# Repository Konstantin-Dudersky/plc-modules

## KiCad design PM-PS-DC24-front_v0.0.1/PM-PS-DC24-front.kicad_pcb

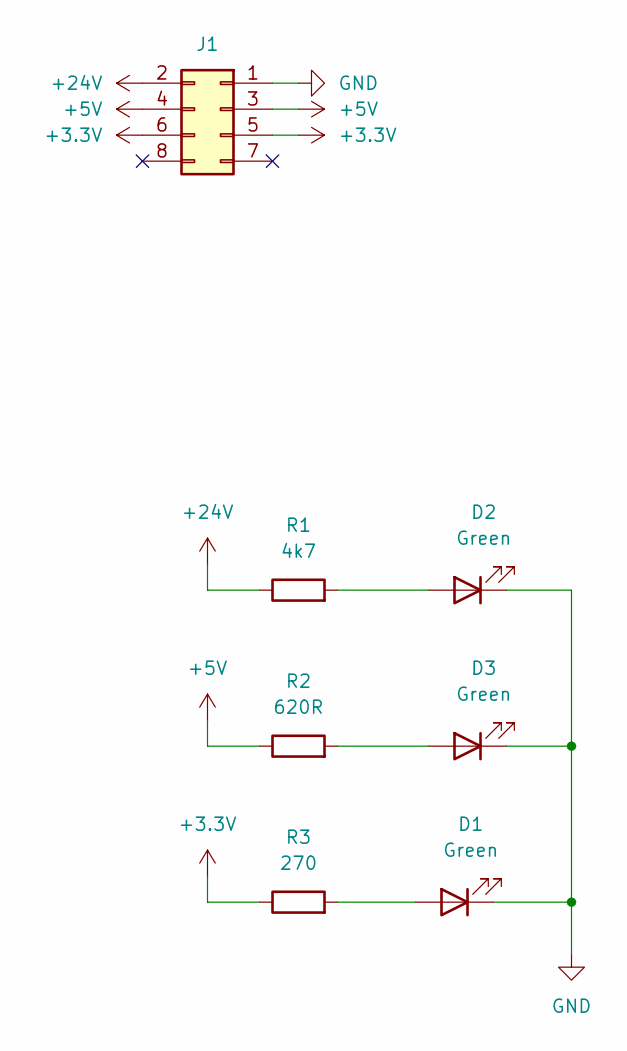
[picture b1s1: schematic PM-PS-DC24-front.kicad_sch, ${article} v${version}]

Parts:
D1, D2, D3: Green; LED_1206_3216Metric_ReverseMount_Hole1.8x2.4mm; part_ipn LED_green_1206_reverse
J1: PinHeader_02x04_P2.54_THT_angle; PinHeader_2x04_P2.54mm_Horizontal; part_ipn PinHeader_02x04_P2.54_THT_angle
R1: 4k7; R_1206_3216Metric_Pad1.30x1.75mm_HandSolder; part_ipn R_4k7_1206_1%
R2: 620R; R_1206_3216Metric_Pad1.30x1.75mm_HandSolder; part_ipn R_620R_1206_1%
R3: 270; R_1206_3216Metric_Pad1.30x1.75mm_HandSolder; part_ipn R_270_1206_1%

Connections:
+3.3V: J1.5, J1.6, R3.1
+5V: J1.3, J1.4, R2.1
+24V: J1.2, R1.1
GND: D1.1 (K), D2.1 (K), D3.1 (K), J1.1
unnamed: D1.2 (A), R3.2
unnamed: D2.2 (A), R1.2
unnamed: D3.2 (A), R2.2

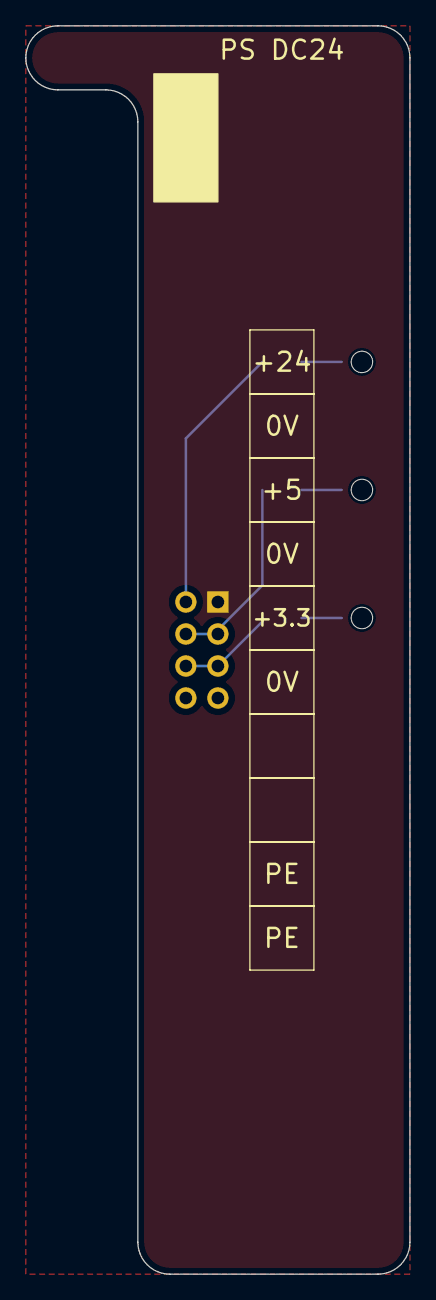
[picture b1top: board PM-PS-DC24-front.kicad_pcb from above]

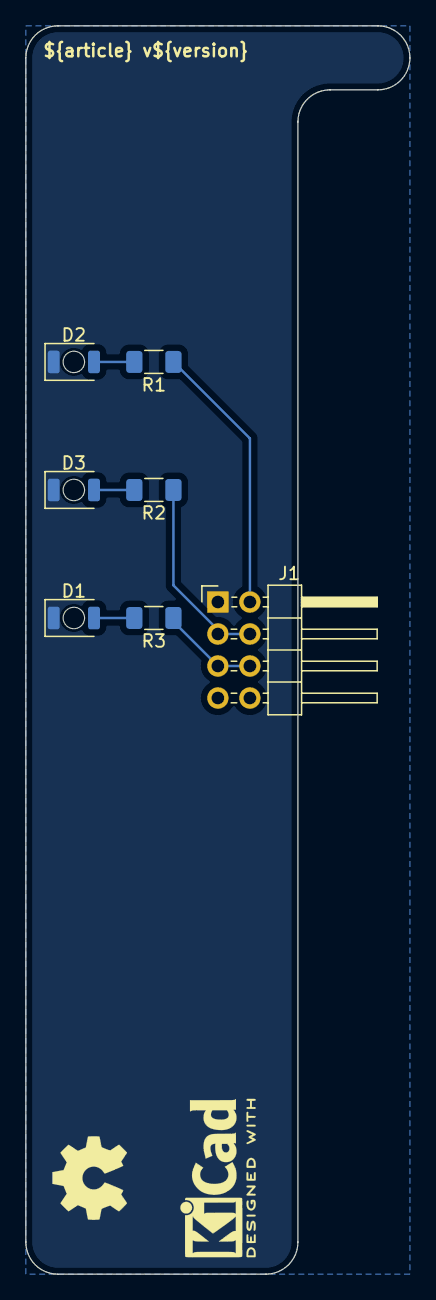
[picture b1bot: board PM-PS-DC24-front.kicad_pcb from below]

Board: 2 copper layers, 30.5 x 99.1 mm, 8 parts (8 on the bottom side), 7 nets.

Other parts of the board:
Logo_kicad: KiCad-Logo2_5mm_SilkScreen

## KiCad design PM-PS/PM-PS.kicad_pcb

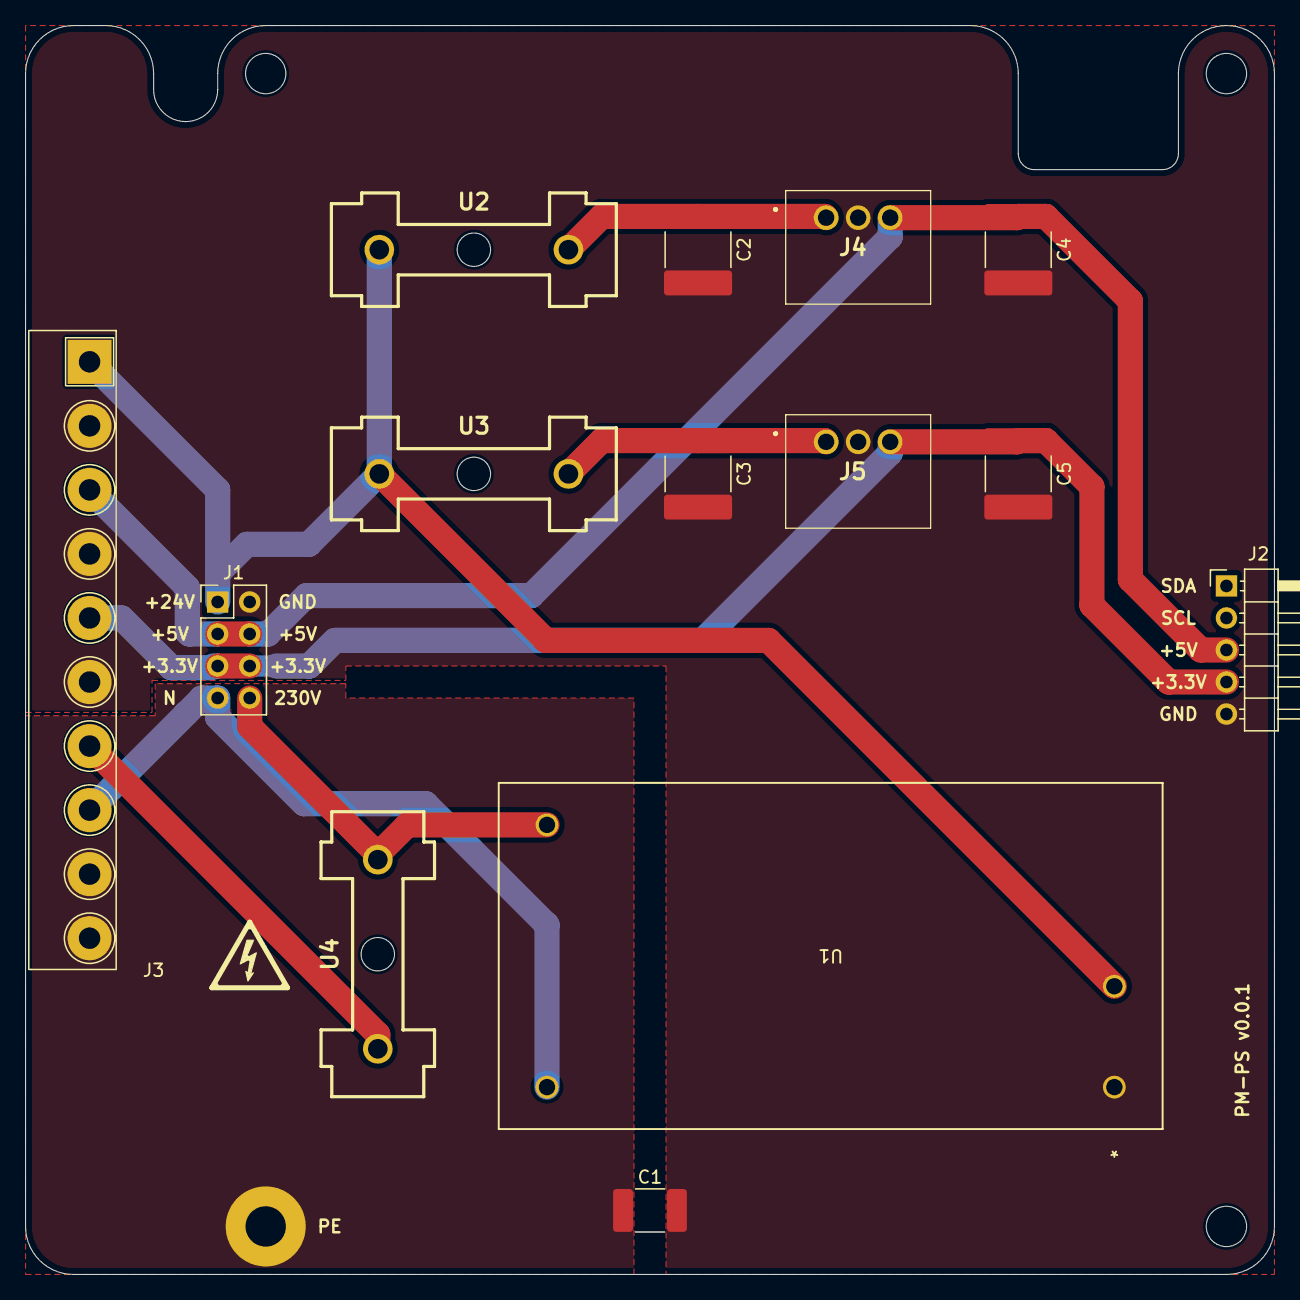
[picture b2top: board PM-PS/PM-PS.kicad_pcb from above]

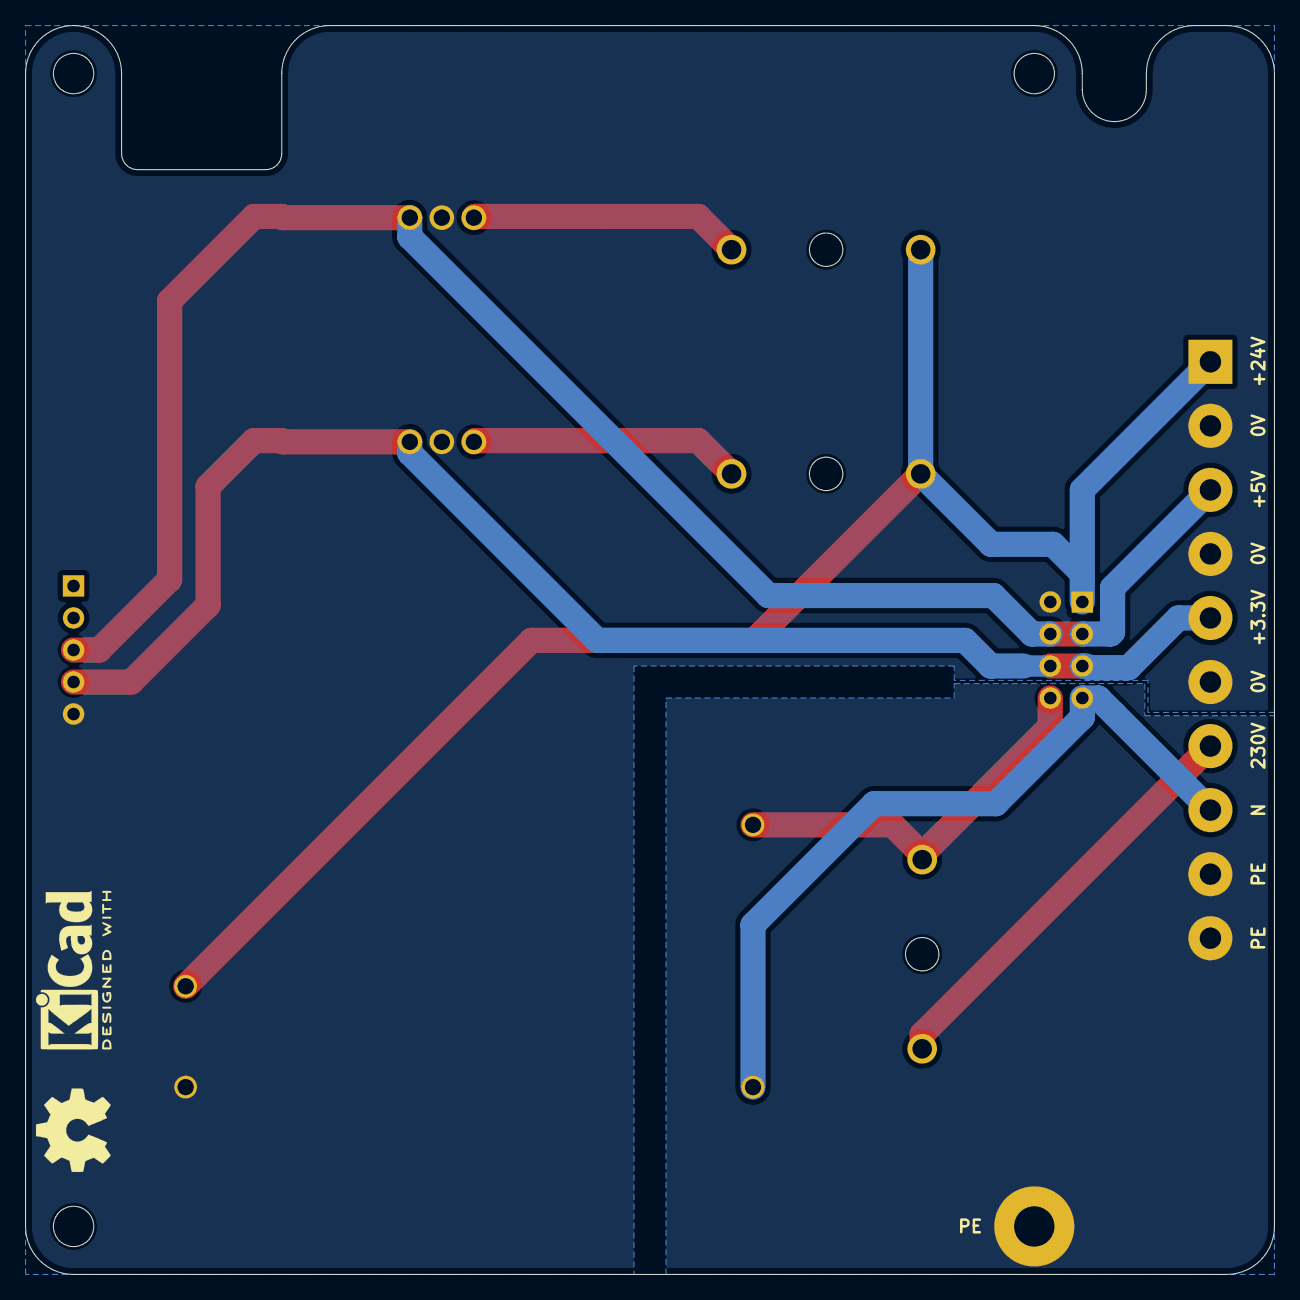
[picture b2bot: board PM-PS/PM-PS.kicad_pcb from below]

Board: 2 copper layers, 99.1 x 99.1 mm, 20 parts (2 on the bottom side), 10 nets.

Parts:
C1: 4.7nF 2kV; C_1812_4532Metric_Pad1.57x3.40mm_HandSolder
C2, C3, C4, C5: 22uF; C_2220_5750Metric_Pad1.97x5.40mm_HandSolder
H1, H2, H3: MountingHole; MountingHole_3.2mm_M3
J1: PM-front-02x04
J2: PinHeader_01x05_P2.54_THT_angle; PinHeader_1x05_P2.54mm_Horizontal
J3: 2EDGR-5.08-10P; Degson_2EDGR-5.08-10P
J4: K7805-2000R3
J5: K7803-2000R3; K7805-2000R3
PE1: PE
U1: IRM-20-24; IRM-20-24_MWU
U2, U3, U4: 64900001039; Fuseholder
kicad_logo: KiCad-Logo2_5mm_SilkScreen
oshw_logo: OSHW-Symbol_6.7x6mm_SilkScreen

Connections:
230V: J1.8, U1.3 (AC/L), U4.2
+3.3V: C5.1, J1.5, J1.6, J2.4, J3.5, J5.3 (+VO)
+5V: C4.1, J1.3, J1.4, J2.3, J3.3, J4.3 (+VO)
+24V: J1.1, J3.1, U1.2 (V+), U2.1, U3.1
GND: C1.2, C2.2, C3.2, C4.2, C5.2, J1.2, J2.5, J3.2, J3.4, J3.6, J4.2 (GND), J5.2 (GND), U1.1 (V-)
N: J1.7, J3.8, U1.4 (AC/N)
unnamed: J3.7, U4.1
unnamed: C2.1, J4.1 (VIN), U2.2
unnamed: C3.1, J5.1 (VIN), U3.2
PE: C1.1, J3.9, J3.10, PE1.1

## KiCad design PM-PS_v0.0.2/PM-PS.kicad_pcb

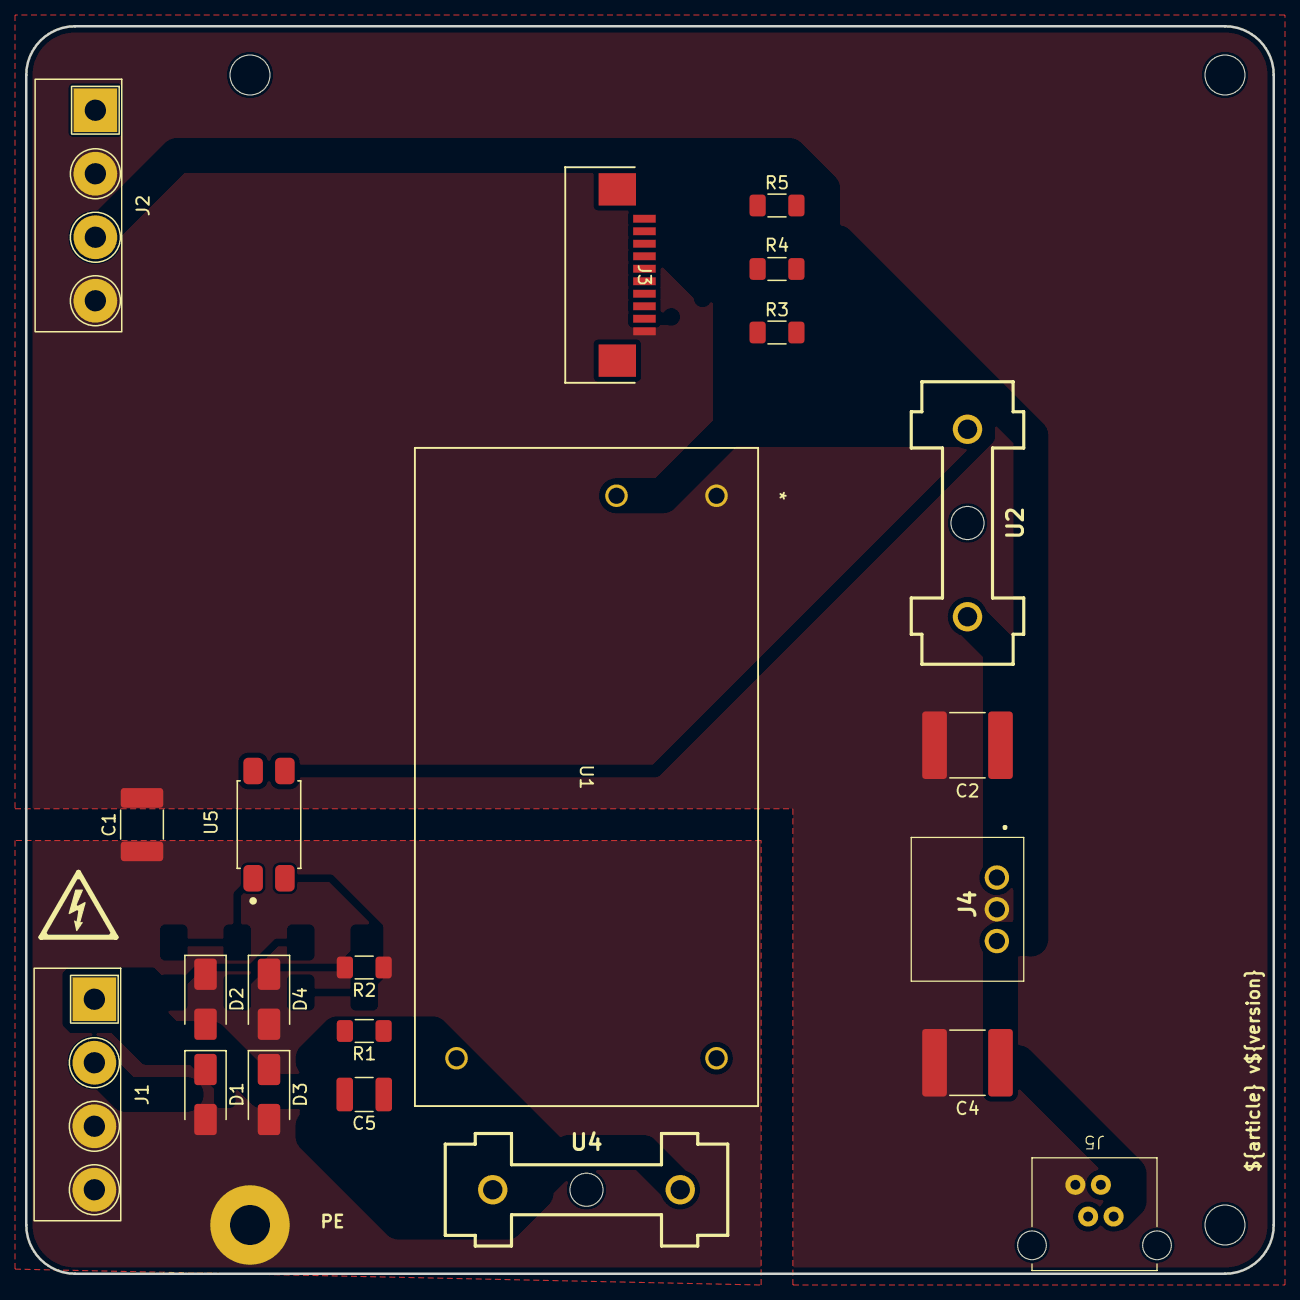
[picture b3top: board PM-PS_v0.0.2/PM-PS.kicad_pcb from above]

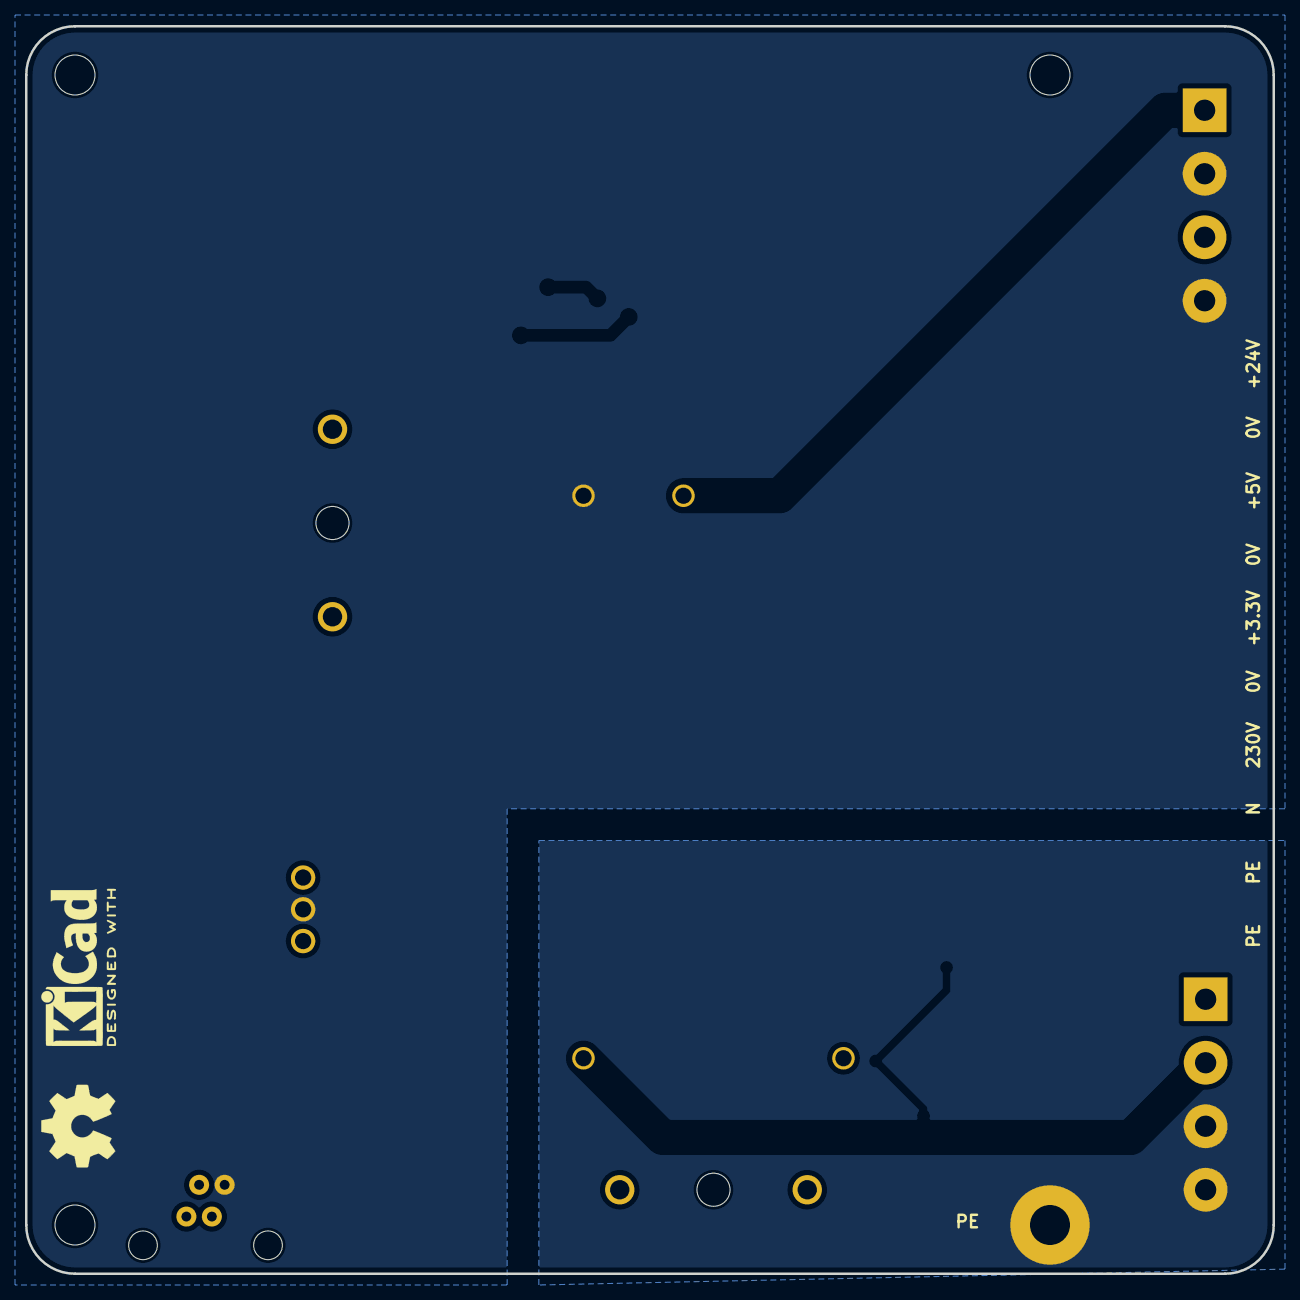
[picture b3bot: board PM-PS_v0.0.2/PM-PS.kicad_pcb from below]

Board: 2 copper layers, 99.8 x 99.8 mm, 29 parts (2 on the bottom side), 16 nets, no tracks yet.

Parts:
C1: 4.7nF 2kV; C_1812_4532Metric_Pad1.57x3.40mm_HandSolder
C2, C4: 22uF; C_2220_5750Metric_Pad1.97x5.40mm_HandSolder
C5: 150nF 630V; C_1210_3225Metric_Pad1.33x2.70mm_HandSolder
D1, D2, D3, D4: 1N4007; D_SMA
H1, H2, H3: MountingHole; MountingHole_3.2mm_M3
J1, J2: 2EDGR-5.08-04P; Degson_2EDGR-5.08-04P
J3: AFA07-S10FCC-00; CONN10_AFA07-S10_JUS
J4: K7805-2000R3
J5: R-RJ11R04P-A802
PE1: PE
R1: 680k; R_1206_3216Metric_Pad1.30x1.75mm_HandSolder
R2: 100; R_1206_3216Metric_Pad1.30x1.75mm_HandSolder
R3, R4: 330R; R_1206_3216Metric_Pad1.30x1.75mm_HandSolder
R5: 4k7; R_1206_3216Metric_Pad1.30x1.75mm_HandSolder
U1: IRM-20-24; IRM-20-24_MWU
U2, U4: 64900001039; Fuseholder
U3: PM-LED8_v0.0.1; PM-LED_v0.0.1
U5: PC817; PC817XI_SOIC254P975X460-4N
kicad_logo: KiCad-Logo2_5mm_SilkScreen
oshw_logo: OSHW-Symbol_6.7x6mm_SilkScreen

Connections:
230V: C5.1, R1.1, U1.3 (AC/L), U4.2
+5V: C4.1, J2.3, J4.3 (+VO), J5.1, R4.1
+24V: J2.1, R5.1, U1.2 (V+), U2.1
/230V_LED: R3.1, U5.3
/subplates/230V_LED: J3.9, R3.2
/subplates/+5V_LED: J3.3, R4.2
/subplates/+24V_LED: J3.2, R5.2
GND: C1.2, C2.2, C4.2, J2.2, J2.4, J3.10, J4.2 (GND), J5.4, U1.1 (V-)
N: J1.2, R2.1, U1.4 (AC/N)
unnamed: D1.2 (A), D3.2 (A), U5.2
unnamed: C5.2, D1.1 (K), D2.2 (A), R1.2
unnamed: D2.1 (K), D4.1 (K), U5.1
unnamed: D3.1 (K), D4.2 (A), R2.2
unnamed: J1.1, U4.1
unnamed: C2.1, J4.1 (VIN), U2.2
PE: C1.1, J1.3, J1.4, PE1.1

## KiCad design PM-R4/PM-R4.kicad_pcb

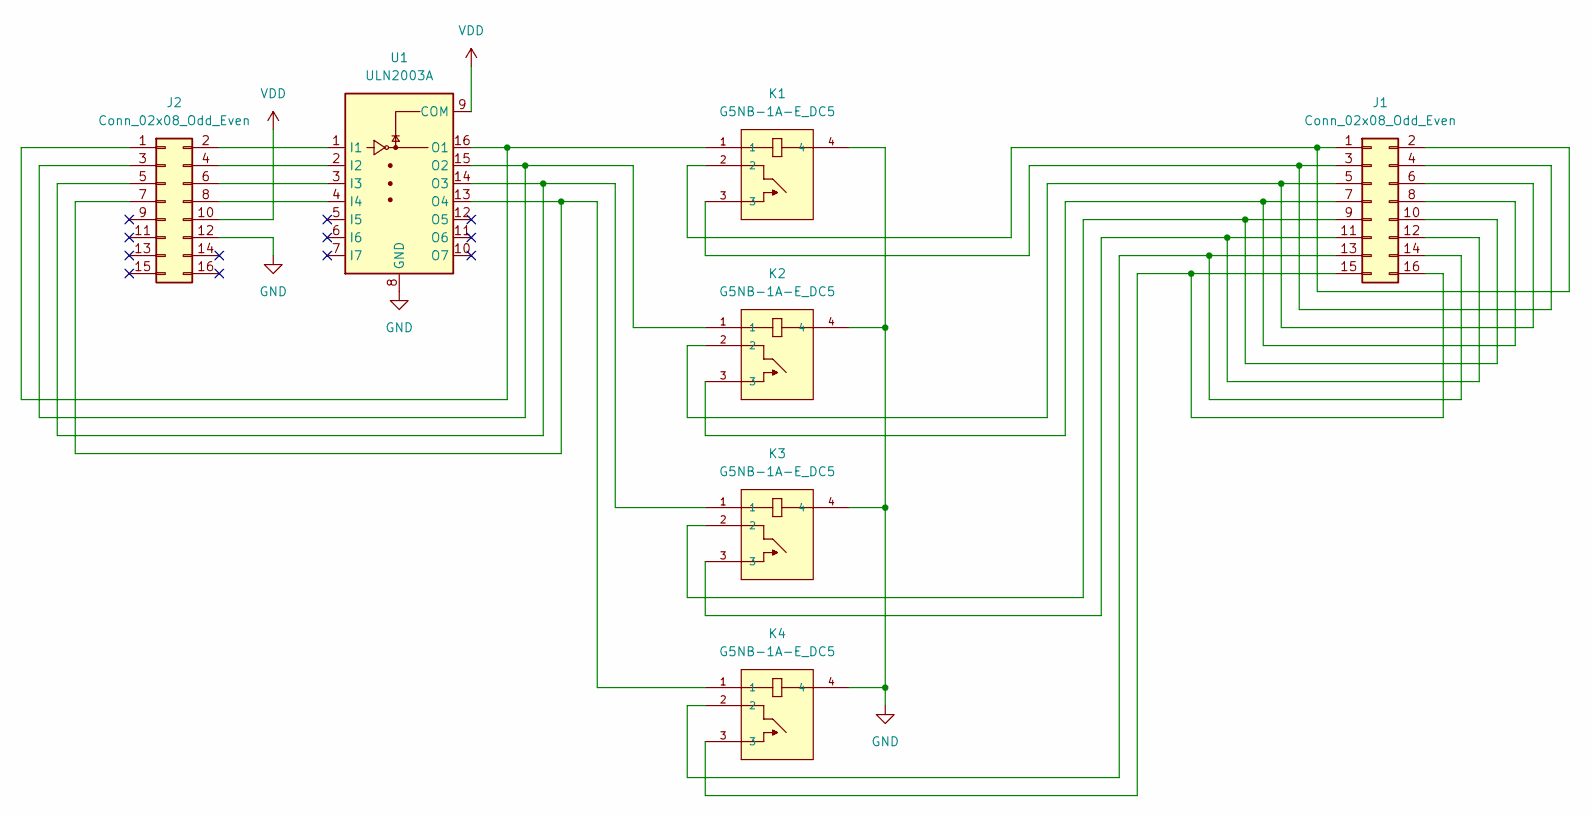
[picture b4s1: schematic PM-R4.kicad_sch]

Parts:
J1, J2: Conn_02x08_Odd_Even; PinHeader_2x08_P2.54mm_Vertical_SMD
K1, K2, K3, K4: G5NB-1A-E_DC5; G5NB-1A-E_DC12_RELAY_G5NB-1A_DC5_OMR; MANUFACTURER_PART_NUMBER G5NB-1A-E DC12
U1: ULN2003A; SOIC-16_3.9x9.9mm_P1.27mm

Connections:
GND: J2.12, K1.4, K2.4, K3.4, K4.4, U1.8 (GND)
unnamed: J1.1, J1.2, K1.2
unnamed: J1.3, J1.4, K1.3
unnamed: J1.5, J1.6, K2.2
unnamed: J1.7, J1.8, K2.3
unnamed: J1.9, J1.10, K3.2
unnamed: J1.11, J1.12, K3.3
unnamed: J1.13, J1.14, K4.2
unnamed: J1.15, J1.16, K4.3
unnamed: J2.1, K1.1, U1.16 (O1)
unnamed: J2.2, U1.1 (I1)
unnamed: J2.3, K2.1, U1.15 (O2)
unnamed: J2.4, U1.2 (I2)
unnamed: J2.5, K3.1, U1.14 (O3)
unnamed: J2.6, U1.3 (I3)
unnamed: J2.7, K4.1, U1.13 (O4)
unnamed: J2.8, U1.4 (I4)
VDD: J2.10, U1.9 (COM)

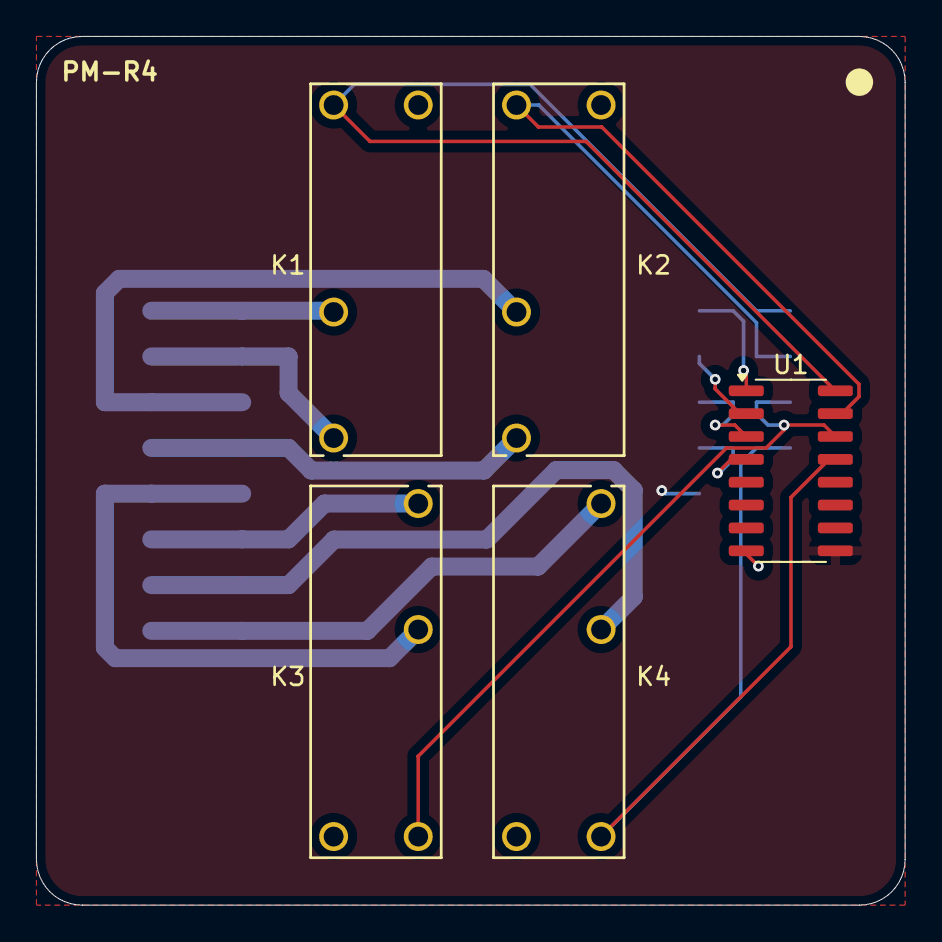
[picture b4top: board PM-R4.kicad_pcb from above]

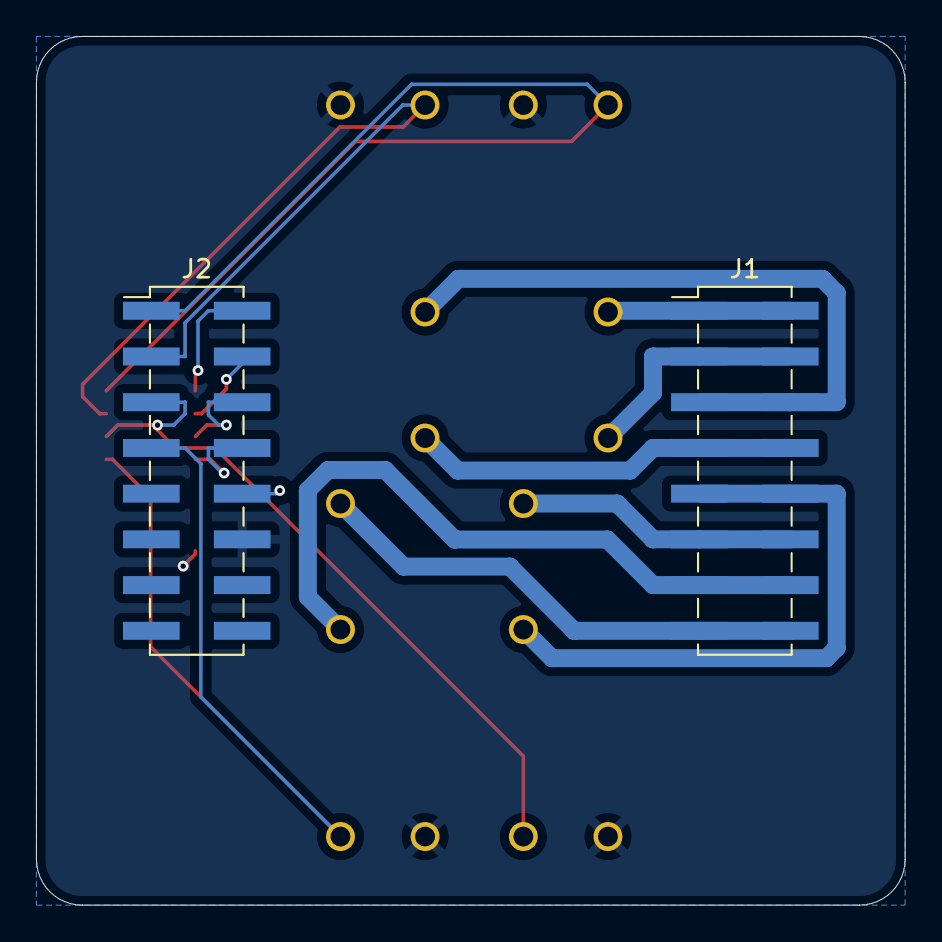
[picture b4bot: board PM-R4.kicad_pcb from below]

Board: 2 copper layers, 48.3 x 48.3 mm, 7 parts (2 on the bottom side), 18 nets.

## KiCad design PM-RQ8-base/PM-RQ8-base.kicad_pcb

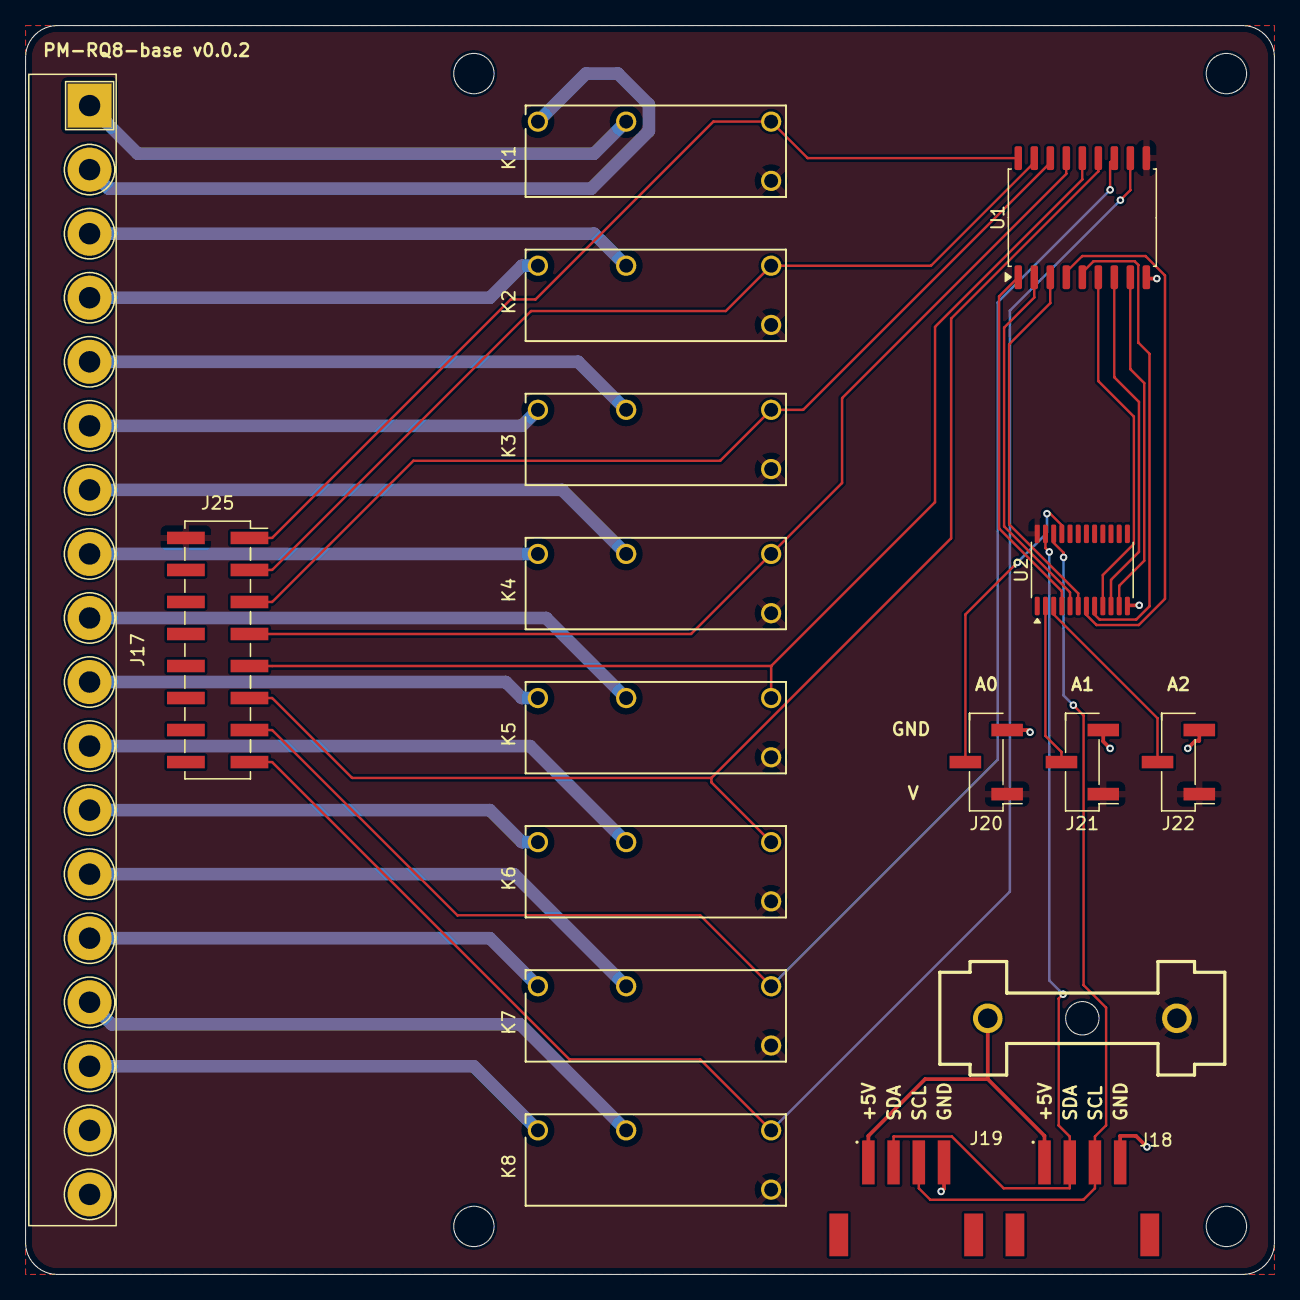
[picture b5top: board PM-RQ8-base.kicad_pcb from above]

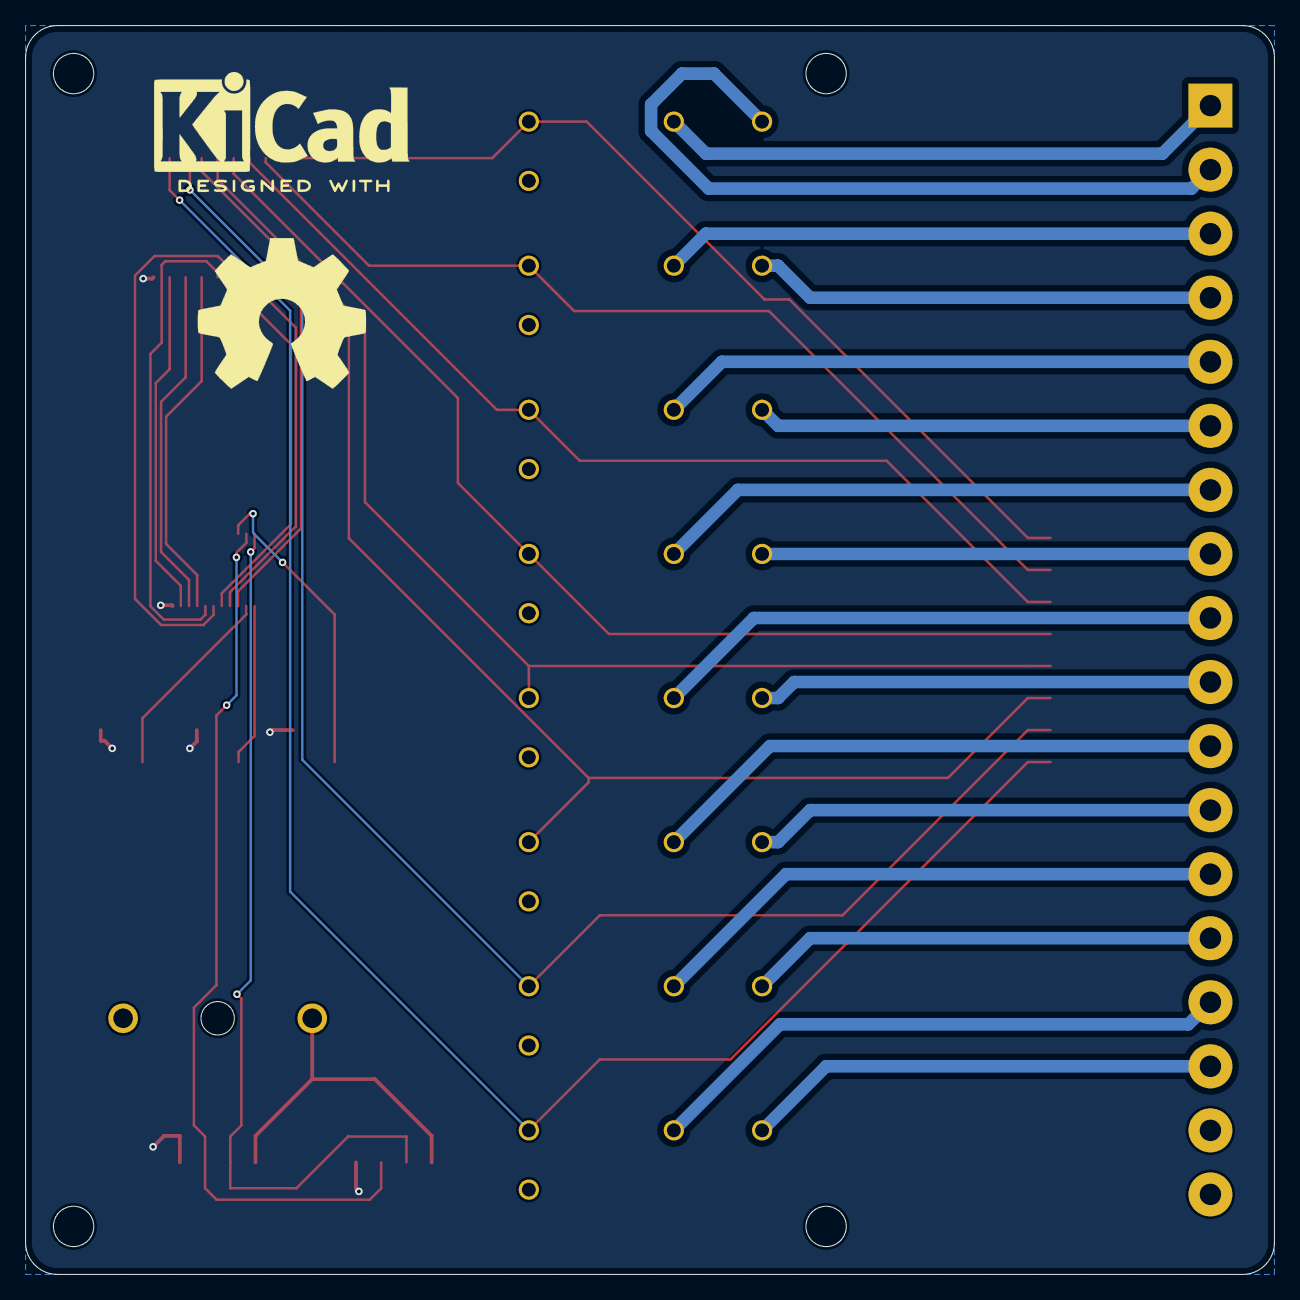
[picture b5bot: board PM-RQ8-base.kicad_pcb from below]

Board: 2 copper layers, 99.1 x 99.1 mm, 24 parts (2 on the bottom side), 40 nets.

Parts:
H1, H2, H3, H4: MountingHole; MountingHole_3.2mm_M3
J17: 2EDGR-5.08-18P; Degson_2EDGR-5.08-18P
J18, J19: S4B-PH-SM4-TB; JST_S4B-PH-SM4-TB_JST_S4B-PH-SM4-TB
J20, J21, J22: Conn_01x03; PinHeader_1x03_P2.54mm_Vertical_SMD_Pin1Left
J25: Conn_02x08_socket; PinSocket_2x08_P2.54mm_Vertical_SMD
K1, K2, K3, K4, K5, K6, K7, K8: G5NB-1A-E_DC5; G5NB-1A-E_DC12_RELAY_G5NB-1A_DC5_OMR
U1: ULN2803A
U2: PCA9555PW; TSSOP-24_4.4x7.8mm_P0.65mm
U3: 64900001039; Fuseholder
logo_kicad: KiCad-Logo2_8mm_SilkScreen
logo_oshw: OSHW-Symbol_13.4x12mm_SilkScreen

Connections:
/A0: J20.2, U2.21 (A0)
/A1: J21.2, U2.2 (A1)
/A2: J22.2, U2.3 (A2)
/K1: J25.1, K1.1, U1.18 (O1)
/K2: J25.3, K2.1, U1.17 (O2)
/K3: J25.5, K3.1, U1.16 (O3)
/K4: J25.7, K4.1, U1.15 (O4)
/K5: J25.9, K5.1, U1.14 (O5)
/K6: J25.11, K6.1, U1.13 (O6)
/K7: J25.13, K7.1, U1.12 (O7)
/K8: J25.15, K8.1, U1.11 (O8)
/SCL: J18.3, J19.3, U2.22 (SCL)
/SDA: J18.2, J19.2, U2.23 (SDA)
GND: J18.4, J19.4, J20.3, J21.3, J22.3, U1.9 (GND), U2.12 (VSS)
unnamed: J17.1, K1.2
unnamed: J17.2, K1.3
unnamed: J17.3, K2.2
unnamed: J17.4, K2.3
unnamed: J17.5, K3.2
unnamed: J17.6, K3.3
unnamed: J17.7, K4.2
unnamed: J17.8, K4.3
unnamed: J17.9, K5.2
unnamed: J17.10, K5.3
unnamed: J17.11, K6.2
unnamed: J17.12, K6.3
unnamed: J17.13, K7.2
unnamed: J17.14, K7.3
unnamed: J17.15, K8.2
unnamed: J17.16, K8.3
unnamed: J18.1, J19.1, U3.2
unnamed: U1.1 (I1), U2.4 (IO0_0)
unnamed: U1.2 (I2), U2.5 (IO0_1)
unnamed: U1.3 (I3), U2.6 (IO0_2)
unnamed: U1.4 (I4), U2.7 (IO0_3)
unnamed: U1.5 (I5), U2.8 (IO0_4)
unnamed: U1.6 (I6), U2.9 (IO0_5)
unnamed: U1.7 (I7), U2.10 (IO0_6)
unnamed: U1.8 (I8), U2.11 (IO0_7)
VDD: J20.1, J21.1, J22.1, J25.2, K1.4, K2.4, K3.4, K4.4, K5.4, K6.4, K7.4, K8.4, U1.10 (COM), U2.24 (VDD), U3.1

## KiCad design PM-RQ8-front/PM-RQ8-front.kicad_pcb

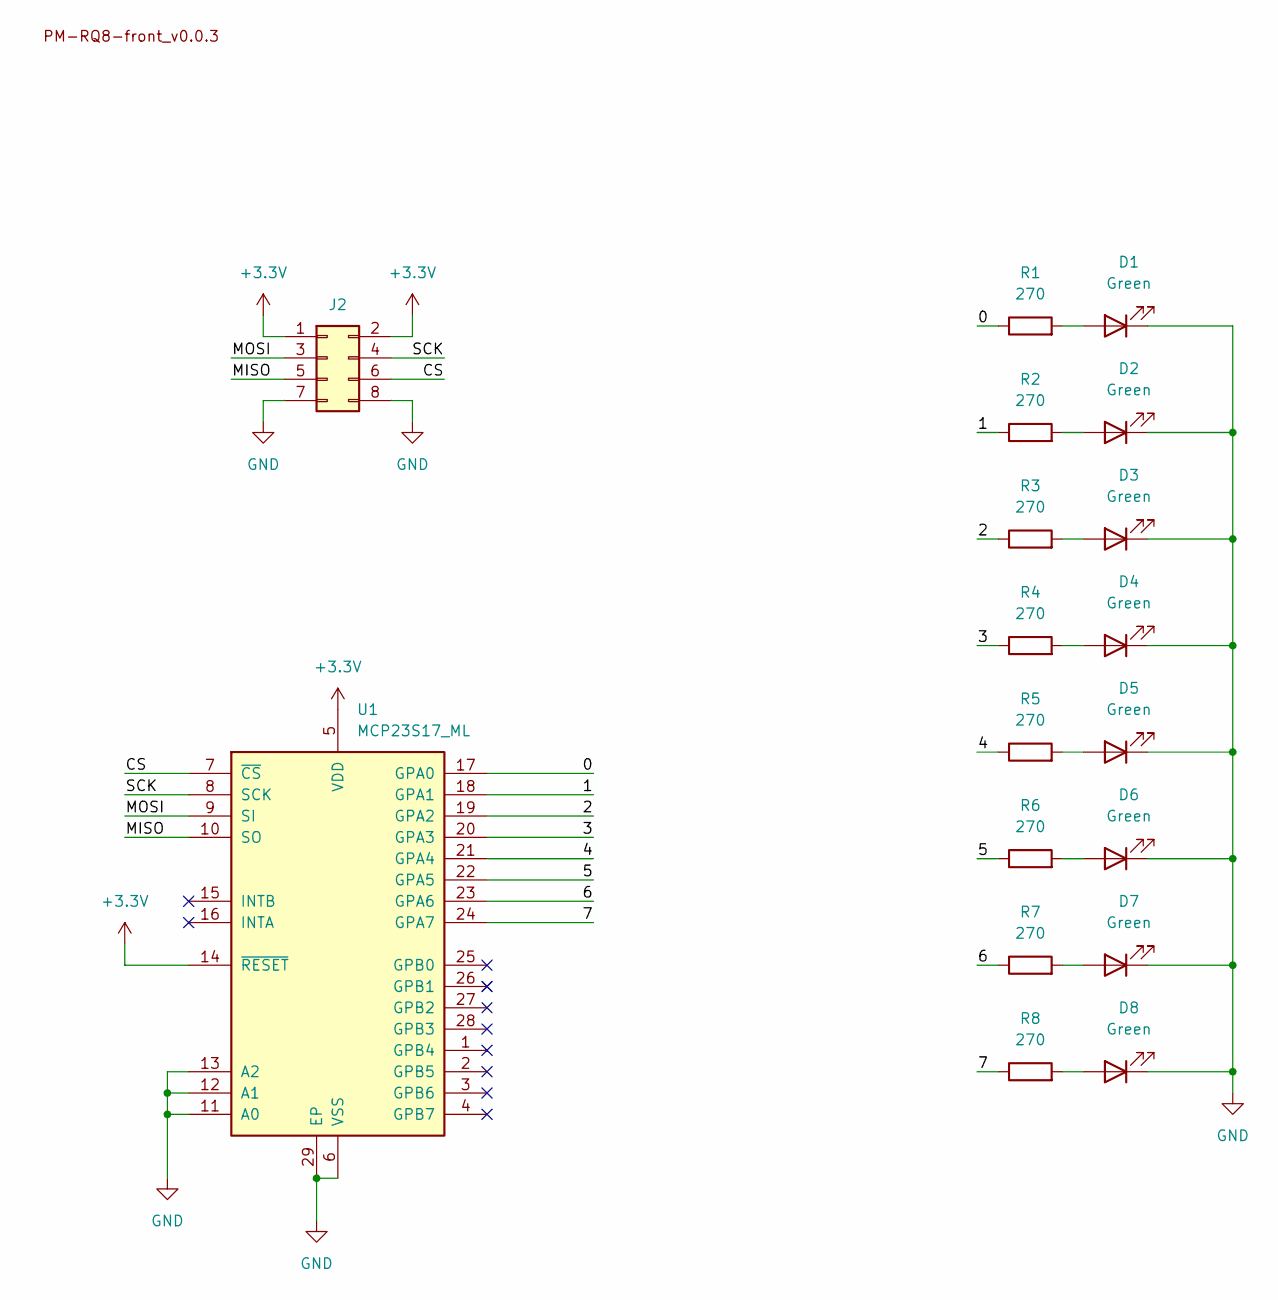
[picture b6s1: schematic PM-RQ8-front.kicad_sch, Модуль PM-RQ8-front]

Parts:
D1, D2, D3, D4, D5, D6, D7, D8: Green; LED_1206_3216Metric_ReverseMount_Hole1.8x2.4mm; part_ipn LED_green_1206_reverse
J2: PinHeader_02x04_P2.54_THT_angle; PinHeader_2x04_P2.54mm_Horizontal; part_ipn PinHeader_02x04_P2.54_THT_angle
PCB1: part_ipn PCB_PM-RQ8-front_v0.0.3
R1, R2, R3, R4, R5, R6, R7, R8: 270; R_1206_3216Metric_Pad1.30x1.75mm_HandSolder; part_ipn R_270_1206_1%
U1: MCP23S17_ML; QFN-28-1EP_6x6mm_P0.65mm_EP4.25x4.25mm; part_ipn MCP23S17-E/ML

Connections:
+3.3V: J2.1, J2.2, U1.5 (VDD), U1.14 (~RESET)
/0: R1.1, U1.17 (GPA0)
/1: R2.1, U1.18 (GPA1)
/2: R3.1, U1.19 (GPA2)
/3: R4.1, U1.20 (GPA3)
/4: R5.1, U1.21 (GPA4)
/5: R6.1, U1.22 (GPA5)
/6: R7.1, U1.23 (GPA6)
/7: R8.1, U1.24 (GPA7)
/CS: J2.6, U1.7 (~CS)
/MISO: J2.5, U1.10 (SO)
/MOSI: J2.3, U1.9 (SI)
/SCK: J2.4, U1.8 (SCK)
GND: D1.1 (K), D2.1 (K), D3.1 (K), D4.1 (K), D5.1 (K), D6.1 (K), D7.1 (K), D8.1 (K), J2.7, J2.8, U1.6 (VSS), U1.11 (A0), U1.12 (A1), U1.13 (A2), U1.29 (EP)
unnamed: D1.2 (A), R1.2
unnamed: D2.2 (A), R2.2
unnamed: D3.2 (A), R3.2
unnamed: D4.2 (A), R4.2
unnamed: D5.2 (A), R5.2
unnamed: D6.2 (A), R6.2
unnamed: D7.2 (A), R7.2
unnamed: D8.2 (A), R8.2

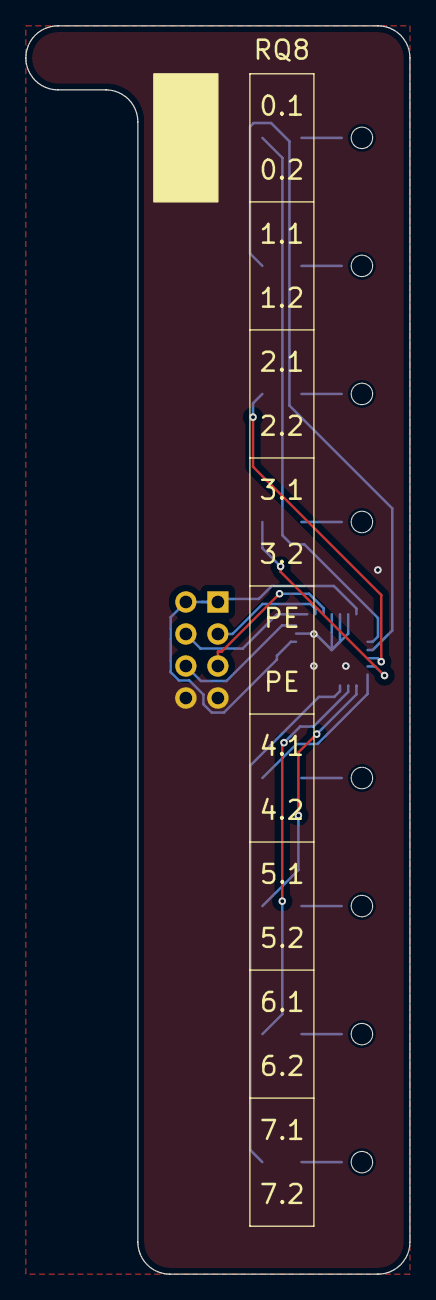
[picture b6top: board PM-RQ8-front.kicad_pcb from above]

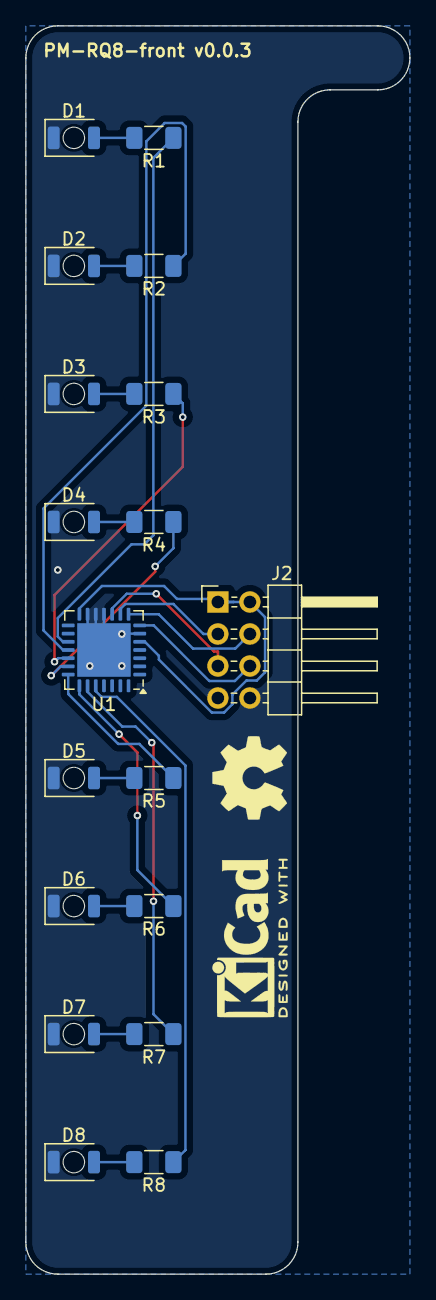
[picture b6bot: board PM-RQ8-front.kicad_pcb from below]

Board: 2 copper layers, 30.5 x 99.1 mm, 19 parts (19 on the bottom side), 22 nets.

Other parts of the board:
Logo_kicad: KiCad-Logo2_5mm_SilkScreen

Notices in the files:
parts and their libraries:
COPYRIGHT: Copyright (C) 2023 Ultra Librarian. All rights reserved.
